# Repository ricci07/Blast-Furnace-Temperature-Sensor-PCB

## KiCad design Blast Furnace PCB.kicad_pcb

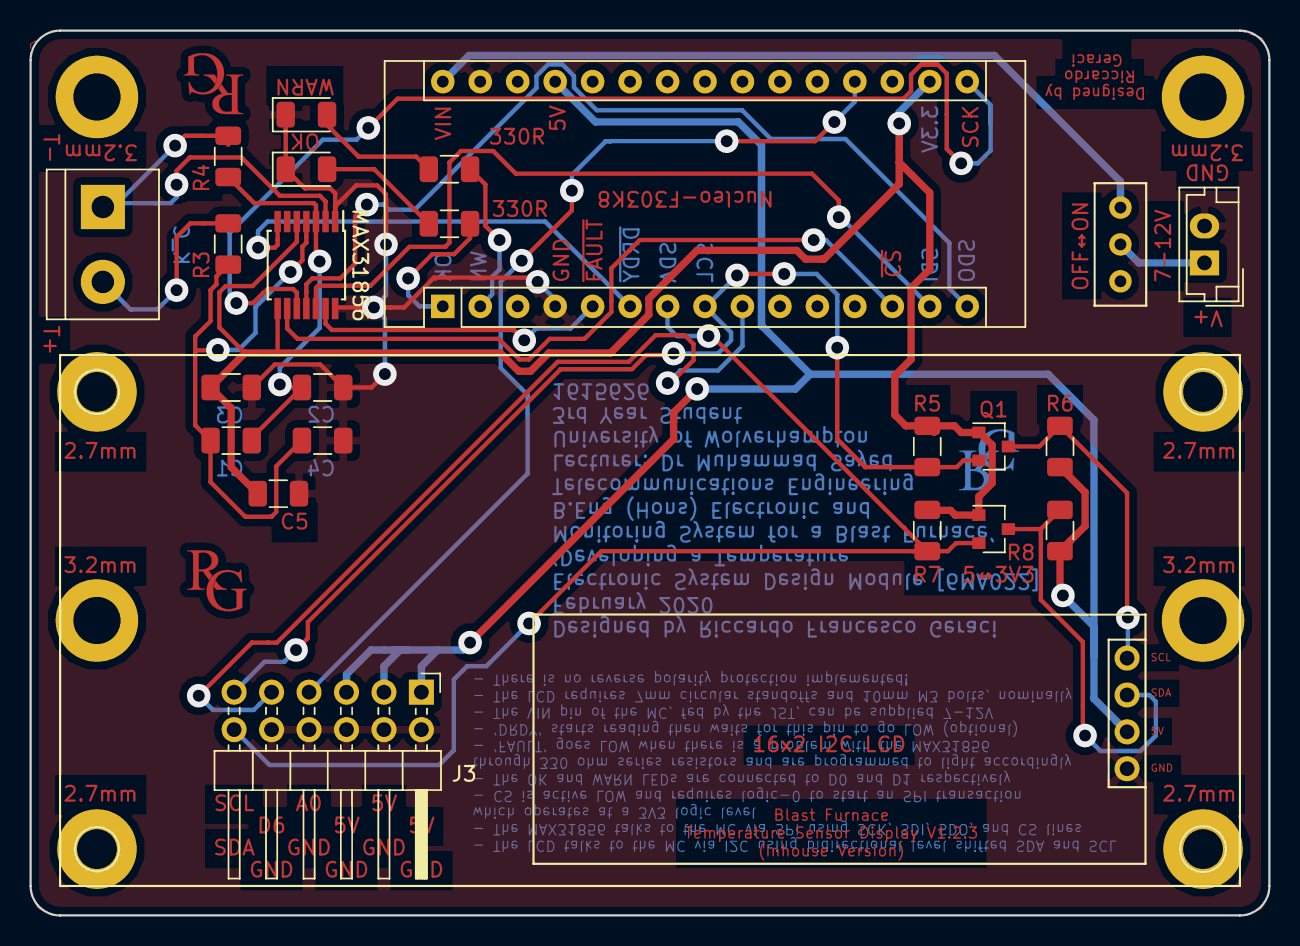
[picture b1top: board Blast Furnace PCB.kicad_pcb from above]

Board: 2 copper layers, 84.0 x 60.0 mm, 35 parts (1 on the bottom side), 25 nets.

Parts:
A1: STM32_Nucleo_F303K8; Arduino_Nano_Header_Nucleo_F303K8
C1, C3, C5: 0.1uF; C_1206_3216Metric
C2, C4: 0.01uF; C_1206_3216Metric
D1: OK_LED; LED_1206_3216Metric
D2: WARN_LED; LED_1206_3216Metric
G1, G1#2, G1#3: LOGO; im calling the police
HL1, HL2, HL4, HL7: MountingHole_2.7mm_Pad
HL3, HL5, HL6, HL8: MountingHole_3.2mm_M3_DIN965_Pad
J1: Thermocouple_Screw_Terminal_01x02; TerminalBlock_bornier-2_P5.08mm
J2: 9V_Conn_01x02; JST_EH_B02B-EH-A_1x02_P2.50mm_Vertical
J3: Conn_02x06_Odd_Even; PinHeader_2x06_P2.54mm_Horizontal
Q1, Q2: BSS138; SOT-23
R1, R2: 330R; R_1206_3216Metric
R3, R4: 100R; R_1206_3216Metric
R5, R6, R7, R8: 10K; R_1206_3216Metric
SW1: POWER_SWITCH; 50VDC_0.5_SPDT_SWITCH
U1: MAX31856; TSSOP-14_4.4x5mm_P0.65mm
U2: I2C_16x2_LCD; 16x2_LCD_I2C_BACKPACK

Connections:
3V3: A1.17, C3.1, C5.1, Q1.1, Q2.1, R5.1, R7.1, U1.5, U1.8
5V: A1.27, J3.1, J3.3, J3.5, R6.1, R8.1, U2.2
/A0: A1.19, J3.7
/CS: A1.13, U1.9
/D6: A1.9, J3.9
/DRDY: A1.6, U1.7
/FAULT: A1.5, U1.13
/SCK: A1.16, U1.10
/SDI: A1.14, U1.12
/SDO: A1.15, U1.11
GND: A1.4, A1.29, C2.2, C3.2, C4.2, C5.2, D1.1, D2.1, J2.2, J3.2, J3.4, J3.6, J3.8, J3.10, U1.1, U1.14, U2.1
unnamed: A1.1, R1.2
unnamed: A1.2, R2.2
unnamed: A1.30, SW1.1
unnamed: C1.1, C4.1, R3.1, U1.4
unnamed: C1.2, C2.1, R4.1, U1.3
unnamed: D1.2, R1.1
unnamed: D2.2, R2.1
unnamed: J1.1, R4.2, U1.2
unnamed: J1.2, R3.2
unnamed: J2.1, SW1.2
SCL_3V3: A1.8, J3.11, Q1.2, R5.2
SCL_5V: Q1.3, R6.2, U2.4
SDA_3V3: A1.7, J3.12, Q2.2, R7.2
SDA_5V: Q2.3, R8.2, U2.3

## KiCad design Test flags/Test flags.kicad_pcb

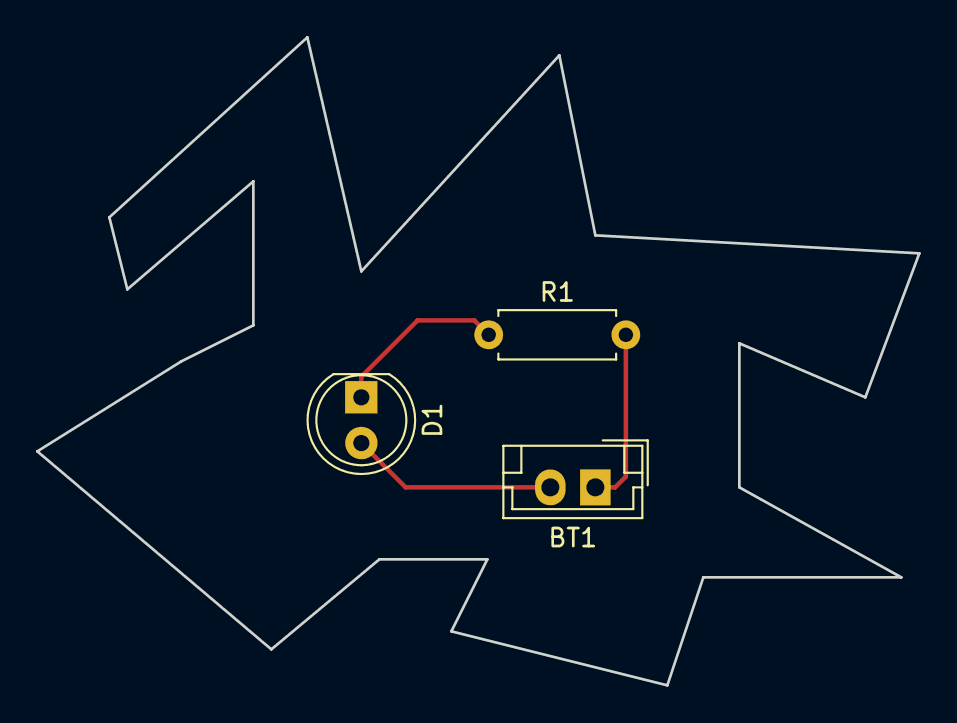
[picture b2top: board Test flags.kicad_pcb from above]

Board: 2 copper layers, 49.0 x 36.0 mm, 3 parts (0 on the bottom side), 3 nets.

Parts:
BT1: 12V; JST_EH_B02B-EH-A_1x02_P2.50mm_Vertical
D1: LED; LED_D5.0mm
R1: 330R; R_Axial_DIN0207_L6.3mm_D2.5mm_P7.62mm_Horizontal

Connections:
unnamed: BT1.1, R1.2
unnamed: BT1.2, D1.2
unnamed: D1.1, R1.1

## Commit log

2020-03-11 After backcopper through hole version send to chris, after I fixed, after I spoke with in lab
2020-03-11 added silly test track
2020-03-11 Connected the missed nucleo pads that were meant to be backcopper as chris' email pointed out and made them all on backcopper as they should have been
2020-03-11 Created gerber files for V1.2.2, and sent to chris
2020-03-11 Nothing much, deleted some old .dxf drill maps
2020-03-12 Increased the size of the LCD pins from 0.8 hole, 1.6 width to 1.0 hole 1.7 wide
2020-03-12 autosave not commited, test again
2020-03-13 standard save stuff
2020-03-27 Added all the mbed code used to program the STM32F303K8
2020-03-27 fixed main.cpp file formatting
